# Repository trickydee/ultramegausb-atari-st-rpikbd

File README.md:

# Atari ST Keyboard (IKBD) Emulator with USB and Bluetooth support

## Overview
This project uses a Raspberry PI PICO to emulate the Atari iKBD keyboard controller and provides USB, Bluetooth and Atari 9 Pin connectivity for devices.

This is useful if you have an Atari Mega ST that is missing its keyboard or if you just want to use modern keyboards, mice and joysticks with your ST.

The emulator provides the ability to use USB or Bluetooth keyboards, mice and joysticks / gamepads with the ST. You can also use original 9 pin Dsub 'Atari' Joysticks!. 

Currently bluetooth requires a Pico 2w device - with this it is possible to Mix and Match any combination of USB, Bluetooth or 9 Pin Atari Joystick peripherals to create your perfect atari setup. If you just want USB support any Pico device will suffice.

The project is based on an an original idea created by 'fieldofcows' in 2020, this project builds on this amazing foundation to improve compatibility, stability and add support for many modern game controllers either wired USB or wireless Bluetooth connected.

A reference hardware design (KiCad schematic and PCB) for the Atari Mega ST, Mega STE, and TT computers is included in the `hardware/` directory, along with Gerber files ready for manufacture at JLCPCB or PCBWAY.

## Contributions

This project is open source and I am happy to receive pull requests and issues to further improve capabilities.

## USB Device Support

* USB HID Keyboards
* USB HID Mice
* USB HID XY Mice - Inc Microsoft Trackballs
* Logitech Unifying Adapter - Keyboard, Mice, Trackball
* Logitech Bolt Adapter - Keyboard, Mice, Trackball

## Game Controller support.
The following USB HID Gamepads/Joysticks are supported (More to come)

* PlayStation 3 DualShock 3 Controllers (including third-party PS3-compatible pads: HORI, Mad Catz, Qanba, Nacon, Logitech F310, etc.)
* PlayStation 4 DualShock 4 Controllers (including third-party PS4-compatible pads: HORI, Razer, Brook, Mad Catz, Qanba, Nacon, PowerA FightPad, etc.)
* PlayStation 5 DualSense and DualSense Edge (USB) (v21.0.3)
* PlayStation Classic (PSC) (v21.0.4)
* Xbox Xinput - Xbox One, Xbox 360 Controllers
* Nintendo Switch Pro Controller (Version 1), Joy-Con (L/R/Pair/Grip), SNES Controller (NSO)
* HORI HORIPAD for Nintendo Switch (v21.0.4)
* PowerA Fusion Wireless Arcade Stick for Nintendo Switch
* Google Stadia Controller
* Nintendo Switch / Wii U GameCube Controller USB Adapter (v11.0.0)

**v21.0.2:** Expanded USB controller support: many additional third-party PS3- and PS4-compatible VID/PIDs (same HID report format as official pads), plus Nintendo Joy-Con Charge Grip and SNES Controller (NSO).

**v21.0.3:** USB support for PlayStation 5 DualSense and DualSense Edge controllers; full joystick mapping and Llamatron dual-stick mode.

**v21.0.4:** USB support for PlayStation Classic (PSC) and HORI HORIPAD for Nintendo Switch; HORIPAD supports Llamatron dual-stick mode.

**v21.0.5:** Build fixes for GCC 15 / current ARM toolchains; `build-all.sh` continues building all board variants if Pico 2 W fails.

**v23.1.0:** Bluetooth reconnect and device-name fixes, restored gamepad routing, stable 115200-baud debug console, and updated Up/Enter/Down hardware buttons. See [release notes](RELEASE_NOTES.md) and [Bluetooth build dependencies](docs/BLUEPAD32_NATIVE_RECONNECT_TEST.md).

**v22.1.1:** Fixes mouse scroll wheel (cursor up/down) and multiple Bluetooth mice when a keyboard is paired; single `handle_keyboard()` per tick.

**v22.1.0:** OLED Devices / Map Devices UI; USB/BT device names on Map Devices; **BLE gamepad pairing fix** for Google Stadia and Xbox Wireless when BLE keyboard/mouse already connected (HID-over-GATT, flash-safe Core 1 timing).

## Bluetooth Support (Pico 2 W only)

The emulator supports Bluetooth keyboards, mice, and gamepads on the Raspberry Pi Pico 2 W (RP2350). This allows you to use wireless devices without USB cables, providing a completely wireless setup for your Atari ST.

### Supported Bluetooth Devices

* **Bluetooth Keyboards**: Standard HID keyboards with full shortcut support (Ctrl+F4, Ctrl+F11, etc.)
* **Bluetooth Mice**: Standard HID mice with scroll wheel support (scroll wheel mapped to cursor up/down keys)
* **Bluetooth Gamepads**: DualSense, DualShock 4, Switch Pro, Xbox Wireless, and more via [Bluepad32](https://github.com/ricardoquesada/bluepad32)

# Usage

## USB
For USB devices, just connect your device via the Pico's USB port using a USB OTG HUB.
The devices listed above will work a few seconds after being connected, you can confirm they are detected on the OLED screen, if you find a modern device that does not let me know via an issue ticket. 

## Bluetooth
### Pairing Bluetooth Devices

Pairing is simple - **just put your device into Bluetooth pairing mode**. The emulator will automatically detect and connect to supported devices. The emulator continuously scans for new devices, so you can pair devices at any time without needing to restart.
Most Bluetooth devices will remain paired and can be unpaired at the device ot by pressing the right - unpair button on the homescreen.

Note: During testing it has been identified that Logitech MX devices require re-pairing after each restart of the emulator.

### Bluetooth Mode Selection

On the splash screen (homescreen), you can use the **left button** to cycle between three modes:
- **USB + Bluetooth** (default): Both USB and Bluetooth devices are active simultaneously
- **USB only**: Only USB devices are used, Bluetooth is disabled
- **Bluetooth only**: Only Bluetooth devices are used, USB is disabled

### Resetting Bluetooth Pairings

If you need to clear stored Bluetooth pairing keys (for example, if a device won't reconnect or you want to re-pair from scratch), press the **right button** on the first splash screen. This will delete all stored Bluetooth pairing information, allowing you to re-pair devices from scratch.

### Bluetooth Gamepad Support

Bluetooth gamepads work just like USB gamepads:
- They appear in the joystick count alongside USB controllers
- They can be assigned to Joystick 0 or Joystick 1 via the OLED interface
- **Llamatron dual-stick mode works with Bluetooth gamepads** (requires exactly one gamepad, USB or Bluetooth)
- All keyboard shortcuts work with Bluetooth keyboards (Ctrl+F4, Ctrl+F11, etc.)

**Note**: Bluetooth support requires a Pico 2 W (RP2350). The original Pico W (RP2040) does not have enough RAM for Bluetooth support.

## Keyboard Shortcuts

The emulator supports several keyboard shortcuts for convenient control:

| Shortcut | Function | Description |
|----------|----------|-------------|
| **Ctrl+F4** | Llamatron Dual-Stick Mode | Share a single dual-stick gamepad (USB or Bluetooth) across Joystick 0 & 1 for Twinstick shooters see Llamatron Dual-Stick Mode section |
| **Ctrl+F8** | Restore Joystick Mode | Sends 0x14 to restore joystick event reporting (useful after reconnect) |
| **Ctrl+F9** | Toggle Joystick 0 | Switches Joystick 0 between D-SUB and USB |
| **Ctrl+F10** | Toggle Joystick 1 | Switches Joystick 1 between D-SUB and USB |
| **Ctrl+F11** | XRESET | Triggers HD6301 hardware reset (like power cycling the IKBD) |
| **Ctrl+F12** | Toggle Mouse Mode | Switches between USB mouse and joystick 0    * |
| **Alt+/** | INSERT Key | Sends Atari ST INSERT key (useful for sending mouse click on Logitech Mac USB keyboards) |
| **Alt+[** | Keypad /** | Sends Atari ST keypad divide key |
| **Alt+]** | Keypad *** | Sends Atari ST keypad multiply key |
| **Alt+Plus** | Set 270MHz | Overclocks RP2040 to 270MHz for maximum performance |
| **Alt+Minus** | Set 150MHz | Sets RP2040 to 150MHz for stability |

### IKBD Command Macros

For reference, these shortcut keys emit the following HD6301/IKBD command sequences:

| Shortcut | Command Sequence | Effect |
| --- | --- | --- |
| `Ctrl+F5` | `0x1A 0x00`, `0x92 0x00`, `0x08` | Disable joystick reporting, enable mouse, enter relative mode |
| `Ctrl+F6` | `0x1A 0x00`, `0x92 0x00`, `0x09 0x02 0x80 0x01 0x90` | Disable joystick, enable mouse, enter absolute mode (640×400) |
| `Ctrl+F7` | `0x1A 0x00`, `0x92 0x00`, `0x0A 0x01 0x01` | Disable joystick, enable mouse, set mouse keycode mode |
| `Ctrl+F8` | `0x14` | Restore joystick event reporting |
| `Ctrl+F11` | `XRESET` line | Full IKBD reset pulse |
| `Alt+/`, `[`, `]` | `0x52`, `0x65`, `0x66` | Insert / keypad divide / keypad multiply |

### DB-9 Mice - Joystick 0

*A real ST keyboard has a single DB-9 socket which is shared between the mouse and Joystick 0. The emulator allows you to have a mouse and joystick plugged in simultaneously but you need to select whether the mouse or joystick 0 is active. This can be toggled by pressing the **Scroll Lock** or  **Ctrl+F12** keys on the keyboard. The current mode is shown on the OLED display.

### Llamatron Dual-Stick Mode

If you love Lammatron and Robotron - Who doesnt ;-) Your going to like Lammatron mode, which enables twinstick functionality for modern controllers.

`Ctrl+F4` enables “Llamatron” mode: if exactly one gamepad (USB or Bluetooth) with two thumbsticks is connected (and both Atari joystick ports are set to USB), the left stick + face buttons continue to drive Joystick 1, the right stick transparently emulates Joystick 0 movement, and the east/right face button (Circle on PlayStation, B on Xbox, A on Switch, B on Stadia) becomes Joystick 0 fire. **How it works:**
- **Left stick** + face buttons control **Joystick 1** (movement and fire)
- **Right stick** controls **Joystick 0** movement
- **Right face button** (Circle on PlayStation, B on Xbox, A on Switch, B on Stadia) becomes **Joystick 0 fire**

**Requirements:**
- Exactly one gamepad connected (USB or Bluetooth)
- Both Atari ST joystick ports must be set to USB mode (via the OLED interface or keyboard shortcuts)
- The gamepad must have two analog thumbsticks

**Automatic deactivation:**
The mode automatically suspends itself if:
- A second gamepad is connected
- Either ST port is switched back to the DB‑9 connector
- The gamepad is disconnected

This feature works seamlessly with both USB and Bluetooth gamepads, allowing you to enjoy twin-stick shooters wirelessly on your Atari ST.

# UI Interface

The emulator displays a simple user interface on an OLED display. This is entirely optional and you can build a working version without it but
it is certainly useful to show successful connection of your USB devices as well as to allow the mouse speed to be tweaked and to view the data
flowing between the emulator and the Atari ST.

The interface is available in English, French, German, Spanish and Italian.

 &emsp;  &emsp; 

 &emsp; 

The emulator supports both USB and Atari ST compatible joysticks, supported a maximum of two joysticks at a time. Using the user interface
you can select whether the USB joystick or Atari joystick are assigned to Joysticks 0 and 1.

# Emulator Hardware

## How it works
The Atari ST keyboard contains an HD6301 microcontroller that can be programmed by the Atari TOS or by user applications to read the keyboard, mouse and joysticks. The keyboard is connected to the Atari via a serial interface (7812.5bps). Commands can be sent from the Atari to the keyboard and the keyboard sends mouse movements, keystrokes and joystick states to the Atari.

Instead of writing code to handle the serial protocol between the Atari and the keyboard, this project provides a full emulation of the HD6301 microcontroller and the hardware connected to it. This means that it appears to the Atari as a real keyboard, and can be customised and programmed by software like a real keyboard, providing maximum compatibility.

The RP2040/RP2350 USB host port or RP2350 Bluetooth is used to connect a keyboard, mouse and joysticks using a USB hub. These are translated into an emulation of the relevant device and fed into the emulated HD6301 control registers, allowing the HD6301 to determine how to communicate this with the Atari.

## Building the emulator Hardware
The emulator is configured as per the schematic below.

All of the external components *except the level shifter* are optional - you do not need to include the display and buttons if you are happy to use the keyboard shortcuts for changing settings. Also, if you only plan to use USB or Bluetooth gamepads / joysticks then you can omit the DB-9 connectors.

The level shifter is required as the Atari uses 5V logic over the serial connection whereas the Pico uses 3.3V logic.

## Hardware PCB Design - Atari Mega Adapter

A reference PCB design is available in KiCad format in the `hardware/` directory for the following Atari computers:

- **Atari Mega ST**
- **Atari Mega STE**
- **Atari TT**

The design includes:
- Complete KiCad project files (schematic and PCB layout)
- Gerber files in the `gerbers/` subdirectory
- A ready-to-upload Gerber zip file: `ultramegausb-atari-mega-adapter-2.2-gerbers.zip`

You can upload the `ultramegausb-atari-mega-adapter-2.2-gerbers.zip` file directly to PCB manufacturers such as [JLCPCB](https://jlcpcb.com/) or [PCBway](https://www.pcbway.com/) to order your own boards.

## Bill of materials

The reference adapter is very simple to construct and is also suprisingly cheap. The table below shows example pricing.
A single adapter can be made for around $20.

| Component                                             | Quantity | Required | Link / Comment                                                | Aprx Cost |
|-------------------------------------------------------|----------|----------|:--------------------------------------------------------------|----------|
| Raspberry PI Pico                                     | 1        | Y         | Pico 2040 / 2350 Module                                       | $7 |
| 1 x 20 Pin 2.54 Single Row Male Pin Header Connector   | 2        | N        | PCB Pico connector - Optional Pico may be soldered to PCB.    | inc with Pico |
| 1 x 20 Pin 2.54 Single Row Female Pin Header Connector | 2        | N        | PCB Pico connector - Optional as Pico may be soldered to PCB. | $7 for 10 |
| Bi-Directional 4 Channel logic level shifter / converter module 3.3v - 5v                           | 1        | Y        |                                                               | $7 for 10 |
| 1 x 6 Pin 2.54 Single Row Male Pin Header Connector   | 2        | Y        | PCB Voltage Regulator connector | inc with Shifter |
| 1 x RJ12 Unshielded 90 Degree push in type 6P6C connector | 1        | Y        | Atari Mega ST/TT Keyboard Connector | $9 for 30 |
| 1 x 6 Pin 2.54 Single Row Female Pin Header Connector | 2        | N        | PCB Voltage Regulator connector | $2 for 20 |
| OLED 0.96" Display 128x64 I2C SSD1306.                | 1        | N        | OLED Display - Blue / White / Yellow + Blue                                                  | $4 |
| 1 x 4 Pin 2.54 Single Row Male Pin Header Connector   | 1        | N        | OLED Connector | inc with OLED |
| Micro Push Button Switch - 6mm x 6mm x5mm             | 3        | N        | OLED Control buttons                                          | $12 for 20 |
| Micro Push Button Switch - 6mm x 6mm x5mm             | 1        | N        | Pico Reset buttons                                            | As Above |
| 1 x 4 Pin 2.54 Single Row Female Pin Header Connector | 1        | N        | PCB OLED connector | $2 for 20 |
| 9 Pin Male D-Sub Socket PCB Board Mount Connector | 2        | N        | 9 Pin Joystick Port | $10.14 for 30! |
| PCB Print at JLPCB | 1        | Y        | Example print  | $10 for 5 |

You will also need a straight through R12 to RJ12 Cable (All 6 pins connected) to connect between the Atari and the Adapter. These can be purchased pre made from Amazon (A modem cable will do if all 6 pins are terminated).

## Building/Compiling the Emulator Firmware

### Mac (ARM)  

Compiling on the mac requires xcode, gcc and arm embedded toolchain. A build can be performed with the following commands:

```bash
# Default: Pico 2 W production only (fastest for BT development)
./build-all.sh

# Incremental rebuild (keeps build/build-pico2_w/ between runs)
CLEAN_BUILD_DIRS=0 ./build-all.sh

# All boards, all in dist/
BUILD_BOARDS=all ./build-all.sh

# Debug OLED screens
DEBUG=1 ./build-all.sh

# French interface
LANGUAGE=FR ./build-all.sh

# Output (default run): dist/atari_ikbd_pico2_w_production.uf2
```

#### `build-all.sh` environment variables

| Variable | Default | Description |
|----------|---------|-------------|
| `BUILD_BOARDS` | `pico2_w` | Board(s) to build: `pico2_w`, comma-separated `pico,pico2,pico_w,pico2_w`, or `all` |
| `BUILD_VARIANT` | `production` | `production` (OLED on, minimal log), `debug` (verbose log), or `speed` (no OLED) |
| `SKIP_VARIANTS` | `1` | `1` = single variant only; `0` = after a debug build, also build production and speed |
| `CLEAN_BUILD_DIRS` | `1` | `1` = wipe build trees before/after; `0` = keep `build/build-*` for incremental rebuilds |
| `DEBUG` | `0` | `1` = debug OLED UI screens (independent of `BUILD_VARIANT`) |
| `LANGUAGE` | `EN` | `EN`, `FR`, `DE`, `SP`, or `IT` |

UF2 files are written to `dist/` with names like `atari_ikbd_pico2_w_production.uf2`. CMake trees live under `build/build-{pico|pico2|pico_w|pico2_w}/`.

PC (Linux)
```
#Install GCC
sudo apt install gcc-arm-none-eabi

#Install cmake
sudo apt install cmake

# Clone the main repo in your home folder
git clone --recursive https://github.com/trickydee/ultramegausb-atari-st-rpikbd.git

# Update submodules
cd ultramegausb-atari-st-rpikbd
git submodule update --init --recursive

# Fix missing hidparser include in CMakeLists.txt (if needed)
# Open file: ultramegausb-atari-st-rpikbd/pico-sdk/src/rp2_common/tinyusb/CMakeLists.txt
If not present, add this line after line 91:  ${PICO_TINYUSB_PATH}/src/class/hid/hidparser/HIDParser.c
You should have:

target_sources(tinyusb_host INTERFACE
            ${PICO_TINYUSB_PATH}/src/portable/raspberrypi/rp2040/hcd_rp2040.c
            ${PICO_TINYUSB_PATH}/src/portable/raspberrypi/rp2040/rp2040_usb.c
            ${PICO_TINYUSB_PATH}/src/host/usbh.c
            ${PICO_TINYUSB_PATH}/src/host/usbh_control.c
            ${PICO_TINYUSB_PATH}/src/host/hub.c
            ${PICO_TINYUSB_PATH}/src/class/cdc/cdc_host.c
            ${PICO_TINYUSB_PATH}/src/class/hid/hid_host.c
            ${PICO_TINYUSB_PATH}/src/class/hid/hidparser/HIDParser.c
            ${PICO_TINYUSB_PATH}/src/class/msc/msc_host.c
            ${PICO_TINYUSB_PATH}/src/class/vendor/vendor_host.c
            )
From your ultramegausb-atari-st-rpikbd folder:
mkdir build
cd build

# Choose one of the cmake command below according to the language and version number you want to display:
cmake -DLANGUAGE=EN .. # For English interface
or
cmake -DLANGUAGE=FR ..  # For French interface
or
cmake -DLANGUAGE=DE ..  # For German interface
or
cmake -DLANGUAGE=SP ..  # For Spanish interface
or
cmake -DLANGUAGE=IT ..  # For Italian interface

make
```

## Downloading the firmware
If you don't know how or can't build the firmware by yourself, please use the builds in the releases link.

## Using the emulator
If you build the emulator as per the schematic, the Pico is powered directly from the Atari 5V supply. The Pico boots immediately but USB enumeration can take a few seconds. Once this is complete, the emulator is fully operational.

## Emulator UI
The user interface has multiple pages that are rotated between by pressing the middle UI button. The first three pages all show the number of connected USB devices at the top but allow configuration of an option below. The pages in order are:

0. **Splash Screen** (ATARI logo): Shows firmware version and connection status. On Pico 2 W builds with Bluetooth support:
   - **Left button**: Cycles between USB+Bluetooth, USB only, and Bluetooth only modes
   - **Right button**: Deletes all stored Bluetooth pairing keys (useful for troubleshooting connection issues)

1. USB Status + Mouse speed. Left and right buttons change allow the mouse speed to be altered.

2. USB Status + Joystick 0 assignment. Left and right buttons toggle between USB joystick and DB-9 joystick.
   
    &emsp; 

3. USB Status + Joystick 1 assignment. Left and right buttons toggle between USB joystick and DB-9 joystick.
   
    &emsp; 

4. If you have a debug version deployed you will see Serial data Tx/Rx between emulator and Atari (Debug builds Only). Data received from the Atari is on the left, data sent to the Atari is on the right.

Note: The serial data page should only be used for ensuring the connection works. Displaying the page slows down the emulator and you may seem some mouse lag whilst it is active.

## USB Controller Support

The emulator supports multiple types of USB game controllers with reliable hot-swapping:

- **Xbox Controllers**: Xbox 360 (wired/wireless), Xbox One, Xbox Series X|S, Original Xbox
- **PS3 DualShock 3**: Full support via USB (wired); includes third-party PS3-compatible pads (HORI, Mad Catz, Qanba, Nacon, Logitech F310, etc.) (v10.0.0, expanded v21.0.2)
- **PS4 DualShock 4**: Full support via USB (wired); includes third-party PS4-compatible pads (HORI, Razer, Brook, Mad Catz, Qanba, Nacon, PowerA FightPad, etc.) (expanded v21.0.2)
- **PS5 DualSense / DualSense Edge**: Full support via USB (wired); D-pad, sticks, Cross/R2 fire, Llamatron dual-stick (v21.0.3)
- **PlayStation Classic (PSC)**: Full support via USB; D-pad, Cross/R2 fire; no analog sticks (v21.0.4)
- **Nintendo Switch Pro Controller**: Full support with analog stick precision and no drift; also Joy-Con (L/R/Pair/Charge Grip) and SNES Controller (NSO) (expanded v21.0.2)
- **HORI HORIPAD (Switch)**: Full support via USB; D-pad/stick, B/R2 fire; Llamatron dual-stick (v21.0.4)
- **PowerA Fusion Wireless Arcade Stick**: Full support for Nintendo Switch arcade sticks (v8.0.0)
- **Google Stadia Controller**: Full support for Stadia controllers (v8.0.0)
- **Nintendo Switch / Wii U GameCube Adapter**: Full support for official Nintendo GameCube controller USB adapter (v11.0.0)
- **Generic HID Joysticks**: Standard USB joysticks and gamepads

## Fixes
The original fieldofcows build had to fix a number of TinyUSB bugs and contained a patched branch of the TinyUSB code. This project uses the latest mainline version of Tiny USB with customizations being externalized,

This build also fixes the following bugs in the original build:
* USB devices are detected more consistenly and faster due to using the newer TinyUSB library.
* The build uses mainline Pico SDK and TinyUSB Libraries
* The Emulator now supports USB devices that enumerate multiple endpoints such as Logitech unifying and bolt adapters.
* Optimizations to Timing for the Atari RX Serial Link lowering checks from 10ms to us - fixing dropped data - 0x14 Joystick mode commands now work consistently (Great news for Ikari Warriors fans).
* Reduced Core1 6301 emulator sleep from 1ms → 250μs (4x improvement)
* Added 6301 buffer reporting.
* Enabled UART FIFO for RX and TX (32X buffer)

## Acknowledgements
The project is based on an an original idea created by 'fieldofcows' in 2020 - https://github.com/fieldofcows/atari-st-rpikb. This project builds on this great foundation to improve compatibility, stability and add support for many modern game controllers either wired USB or wireless Bluetooth connected.

The "ultramegausb" title is tongue in cheek and intended to highlight the massively enhanced capabilities made possible by the great work of TinyUSB project, Bluepad32 and associated projects listed below.

The project uses code extracted from [Steem SSE](https://sourceforge.net/projects/steemsse/). All of the work of wiring up the keyboard functions to the HD6301 CPU is credited to Steem SSE. This project contains a stripped-down version of this interface, connecting it to the Raspberry Pi's serial port.

Steem itself uses the HD6301 emulator provided by sim68xx developed by Arne Riiber. The original website for this seems to have gone but an archive can be found [here](http://www.oocities.org/thetropics/harbor/8707/simulator/sim68xx/).

The code to handle the OLED display is Copyright (c) 2021 David Schramm and taken from https://github.com/daschr/pico-ssd1306.

Bluetooth support is provided by the Bluepad32 project by Ricardo Quesada https://github.com/ricardoquesada/bluepad32.

Multi-language build support was added by Klyde https://github.com/klyde2278/atari-st-rpikb who also sells a nice kit and device to run this firmware on.

To create this ultramegausb build I also relied on the following projects for inspiration and reference implementations:

- **[tusb_xinput](https://github.com/Ryzee119/tusb_xinput)** by Ryzee119 - TinyUSB XInput host driver used for Xbox controller support
- **[BetterJoy](https://github.com/Davidobot/BetterJoy)** by Davidobot - Reference implementation for Nintendo Switch Pro Controller USB initialization and protocol handling
- **[stadia-vigem](https://github.com/walkco/stadia-vigem)** by walkco - Complete USB HID report format and button mapping for Google Stadia Controller support
- **[wii-u-gc-adapter](https://github.com/ToadKing/wii-u-gc-adapter)** by ToadKing - Linux driver for Wii U GameCube adapter, reference for USB protocol and report format
- **[osx-wiiu-gcc-adapter](https://github.com/area/osx-wiiu-gcc-adapter)** by area - macOS userspace driver for GameCube adapter using async interrupts

A large portion of the code was generated using Cursor AI and Claude LLM.

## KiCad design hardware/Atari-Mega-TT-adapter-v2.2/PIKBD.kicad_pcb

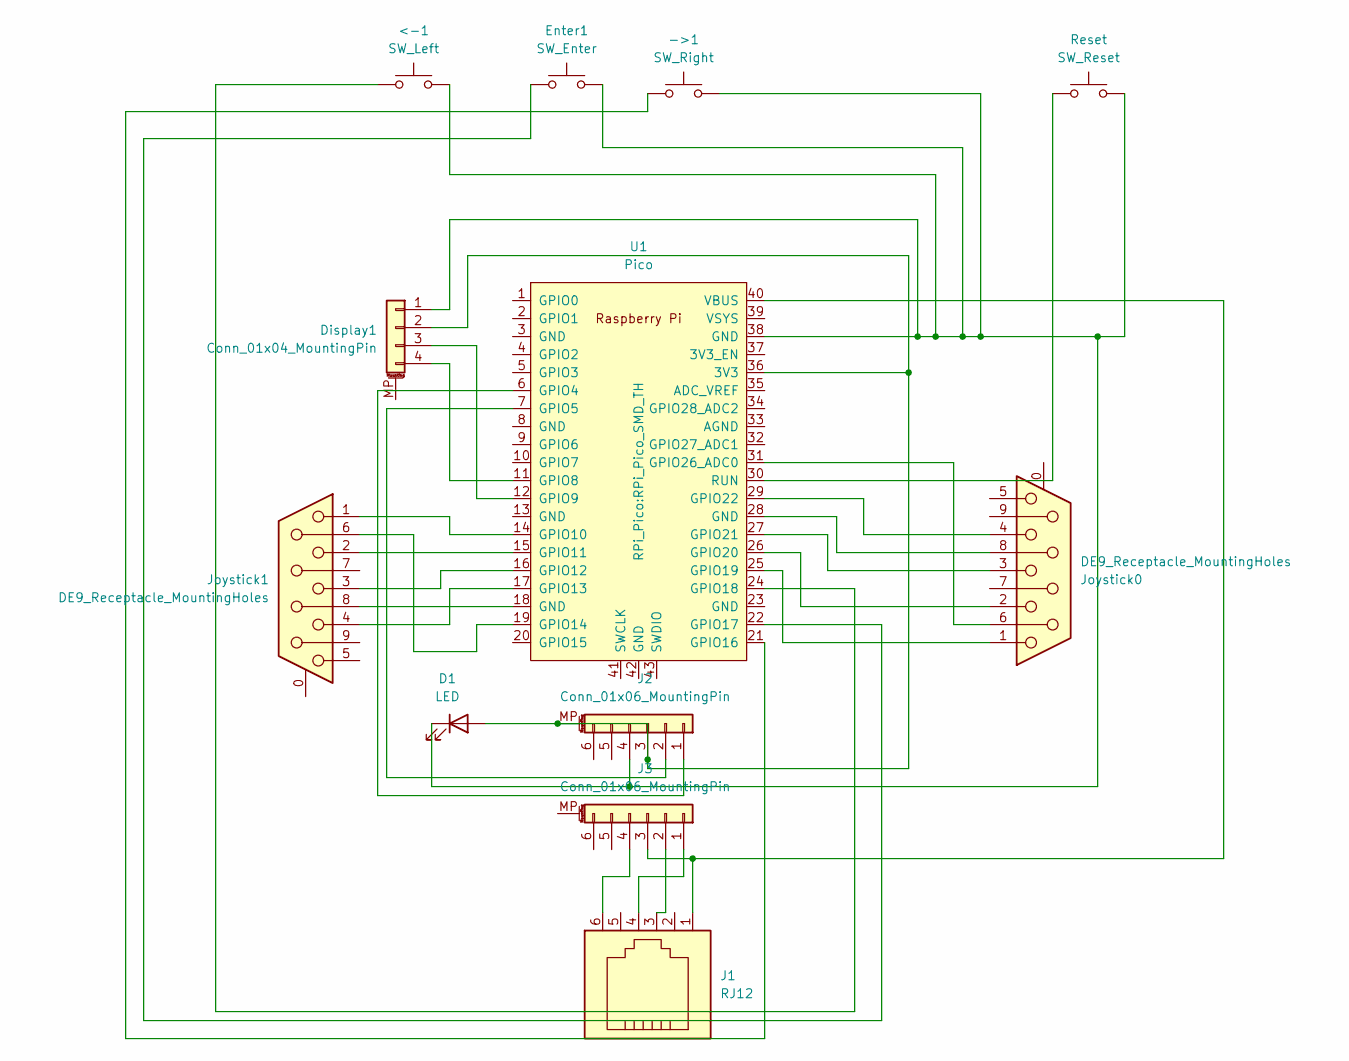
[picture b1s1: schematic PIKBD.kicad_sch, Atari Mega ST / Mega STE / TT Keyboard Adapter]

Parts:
->1: SW_Right; SW_PUSH_6mm
<-1: SW_Left; SW_PUSH_6mm
D1: LED; LED_D3.0mm
Display1: Conn_01x04_MountingPin; PinSocket_1x04_P2.54mm_Vertical
Enter1: SW_Enter; SW_PUSH_6mm
J1: RJ12; RJ12_Amphenol_54601-x06_Horizontal
J2, J3: Conn_01x06_MountingPin; PinSocket_1x06_P2.54mm_Vertical
Joystick0, Joystick1: DE9_Receptacle_MountingHoles; DSUB-9_Male_Horizontal_P2.77x2.84mm_EdgePinOffset7.70mm_Hou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
Reset: SW_Reset; SW_PUSH_6mm
U1: Pico; RPi_Pico_SMD_TH

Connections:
unnamed: D1.2 (A), Display1.2, J2.3, J2.MP (MountPin), U1.36 (3V3)
unnamed: ->1.2, <-1.2, D1.1 (K), Display1.1, Enter1.2, J2.4, Reset.2, U1.38 (GND)
unnamed: Display1.3, U1.12 (GPIO9)
unnamed: Display1.4, U1.11 (GPIO8)
unnamed: J2.1, U1.6 (GPIO4)
unnamed: J2.2, U1.7 (GPIO5)
unnamed: J1.4, J3.1
unnamed: J1.3, J3.2
unnamed: J1.1, J3.3, U1.40 (VBUS)
unnamed: J1.6, J3.4
unnamed: Joystick0.8, U1.28 (GND)
unnamed: Joystick1.8, U1.18 (GND)
unnamed: Joystick1.1, U1.14 (GPIO10)
unnamed: Joystick1.2, U1.15 (GPIO11)
unnamed: Joystick1.3, U1.16 (GPIO12)
unnamed: Joystick1.4, U1.17 (GPIO13)
unnamed: Joystick1.6, U1.19 (GPIO14)
unnamed: ->1.1, U1.21 (GPIO16)
unnamed: Enter1.1, U1.22 (GPIO17)
unnamed: <-1.1, U1.24 (GPIO18)
unnamed: Joystick0.1, U1.25 (GPIO19)
unnamed: Joystick0.2, U1.26 (GPIO20)
unnamed: Joystick0.3, U1.27 (GPIO21)
unnamed: Joystick0.4, U1.29 (GPIO22)
unnamed: Joystick0.6, U1.31 (GPIO26_ADC0)
unnamed: Reset.1, U1.30 (RUN)

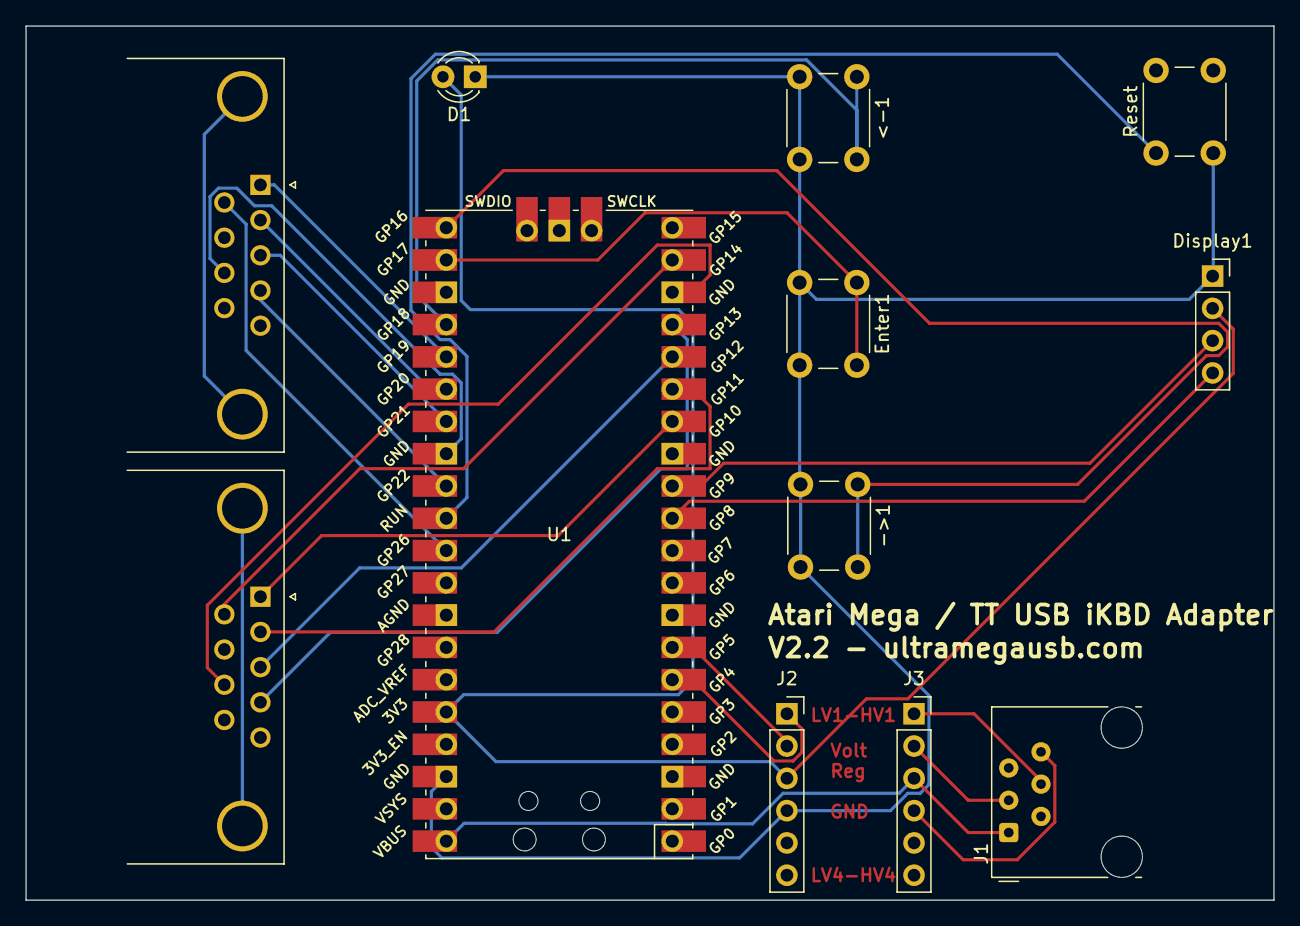
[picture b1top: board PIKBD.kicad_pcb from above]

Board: 2 copper layers, 98.2 x 68.8 mm, 12 parts (0 on the bottom side), 26 nets.

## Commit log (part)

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2025-05-20 Updates, CPU overclocked to 250mhz, USB Mouse mode configured as default (scrlck to swap
2025-05-30 Update UserInterface.h
    Added get_translation function
2025-05-30 Update README.md
    Added translated interface
2025-07-18 Update HidInput.cpp
    Added USB Joystick Dead zone
2025-10-08 Fix USB HID device detection and report handling
    - Upgrade TinyUSB from 0.10.1 to 0.12.0 for better RP2040 support
    - Fix tusb_init() return type check (bool not tusb_error_t)
    - Remove stdio_init_all() and all printf() in HID callbacks to prevent lockups
    - Add explicit tuh_hid_receive_report() calls to start report flow
    - Queue next report after each received report for continuous operation
    - Re-enable HID parser for mice and joysticks (needed for proper handling)
2025-10-08 FINAL: Upgrade to TinyUSB 0.19.0 (June 2024) - Latest Version!
    Renamed wrapper function to avoid API collision:
    - tuh_hid_get_report() → hid_app_request_report()
    - Updated all calls in HidInput.cpp
    - TinyUSB 0.19.0 repurposed tuh_hid_get_report() for control endpoint operations
    COMPLETE MODERNIZATION ACHIEVED:
    ======================================
2025-10-08 Add automated patch system for build compatibility
    - Created patches/pioasm-cmake-fix.patch to fix CMake 4.x compatibility
    - Added apply-patches.sh script to automatically apply patches
    - Updated CMakeLists.txt to run patches before building
    - Reset pico-sdk to official 1.5.1 release (no custom commits)
    - This ensures clean builds work with newer CMake versions
2025-10-11 Add dynamic clock speed control feature
    - Added Alt+Plus (=) keyboard shortcut to set clock to 270MHz
    - Added Alt+Minus (-) keyboard shortcut to set clock to 150MHz
    - Allows testing clock speed impact on joystick timing without reflashing
    - Set default clock speed to 150MHz for better timing stability
    - Prevents Alt+Plus/Minus from being sent to Atari when used for control
2025-10-14 Clean up documentation and build files
    - Add trailing newlines to markdown documentation files
    - Update pico-sdk submodule state
    - Maintain consistency across all project files
2025-10-15 Optimize HD6301 emulator Core 1 performance - v4.0.0
    Major performance improvements for IKBD command processing:
    1. Reduced CYCLES_PER_LOOP from 1000 to 250:
    - Core 1 wakes 4x more frequently (every 250μs instead of 1ms)
    - Serial interrupts processed within 250μs (was 1ms)
    - Multi-byte IKBD commands delivered 4x faster
    - ROM firmware receives command parameters promptly
2025-10-15 Xbox Controller: Add endpoint discovery and comprehensive OLED diagnostics
    Enhanced Xbox detection with automatic endpoint discovery and detailed
    OLED feedback for debugging without console access.
    Endpoint Discovery:
    - Reads configuration descriptor to find actual endpoint addresses
    - Parses descriptor to locate vendor-specific interfaces
    - Extracts IN and OUT endpoint addresses
2025-10-16 Optimize PS4 controller performance - eliminate input lag
    - Increased deadzone from 32 to 50 to eliminate stick drift
    - Removed blocking OLED updates (was updating every 50 reports)
    - Removed 3-second sleep on first report detection
    - Disabled serial debug output (printf) for performance
    - Changed debug from every 50 reports to disabled (#if 0)
    - Applied same optimizations to Xbox controller code
2025-10-16 Fix Caps Lock toggle behavior and USB LED control
    Fixed two issues with Caps Lock:
    1. Required two presses to toggle - now works on single press
    2. USB keyboard LED didn't light - now controls LED properly
    Changes:
    - Send momentary pulse to Atari ST instead of persistent state
    - capslock_send_pulse flag controls when key press is sent
2025-10-16 Fix Logitech Unifying wireless mouse detection
    Root cause: Mouse interface was detected and parsed correctly, but the
    mounted callback was only called for the first interface per device.
    On Logitech Unifying receivers:
    - Instance 0 = Keyboard (first interface, callback called)
    - Instance 1 = Mouse (second interface, callback NOT called)
    Without the mounted callback, the mouse never got added to the device
2025-10-17 Integrate official tusb_xinput driver (Ryzee119)
    Replaced custom Xbox controller detection with official tusb_xinput library:
    https://github.com/Ryzee119/tusb_xinput
    Changes:
    - Downloaded xinput_host.c and xinput_host.h from upstream
    - Added CFG_TUH_XINPUT=2 to tusb_config.h
    - Increased CFG_TUH_ENUMERATION_BUFSIZE to 512 (Xbox 360 Wireless needs >321)
2025-10-22 Update README.md for v7.5.0 and add credits
    - Updated version to 7.5.0
    - Added Nintendo Switch Pro Controller to supported controllers list
    - Added Credits section with thanks to:
    * tusb_xinput by Ryzee119 (Xbox controller support)
    * BetterJoy by Davidobot (Switch Pro Controller reference)
    - Updated controller support section with v7.5.0 features
2025-10-25 Remove QUICK_START.txt
    - Removed outdated quick start file
    - README.md now contains all necessary setup information
2025-10-25 Add automatic submodule initialization to build-all.sh
    - Check if pico-sdk is initialized before building
    - Automatically run 'git submodule update --init --recursive' if needed
    - Makes the build script self-contained for fresh checkouts
2025-10-27 Improve Switch controller splash screen and reduce init delay
    - Changed splash screen from 'SWITCH' to 'SWITCH!' (matching Xbox/PS4 style)
    - Added 2-second display time for consistency with other controllers
    - Reduced Pro Controller initialization delay from 3s to 1s
    - Faster controller initialization without compromising reliability
    - Updated UI countdown timer to reflect 1-second delay
2025-10-30 Add documentation for PowerA and v8.0 changes
2025-10-30 v9.1.0-dev: Add PS3 DualShock 3 controller support (skeleton)
    - Created ps3_controller.h with controller definitions
    - Created ps3_controller.c with basic parsing structure
    - Integrated PS3 detection into hid_app_host.c
    - Added PS3 joystick handler to HidInput.cpp
    - Updated CMakeLists.txt to include ps3_controller.c
    - Updated build-all.sh for debug mode and version
2025-11-02 Update README: Add GameCube adapter support in v11.0.0
    - Add Nintendo Switch/Wii U GameCube Controller USB Adapter to supported controllers
    - Credit ToadKing's Linux driver (wii-u-gc-adapter)
    - Credit area's macOS driver (osx-wiiu-gcc-adapter)
    - Note v11.0.0 release for GameCube adapter support
2025-11-05 chore: Bump version to 12.0.0
    Version 12.0.0 includes:
    - Ultra-low latency serial optimizations (100μs Core 1 cycles)
    - 32-byte software RX queue for zero packet loss
    - UART hardware error detection
    - Optimized 6301 emulator instruction execution
    - GameCube controller debug cleanup
2025-11-07 Tidy up markup documents
2025-11-17 remove dist content
2025-11-19 v14.0.4: Disable all GameCube debug messages for performance
    - Commented out all GC: Report, GC: Received, GC: Report callback, and GC: OUTPUT messages
    - These messages were causing serial console spam and impacting performance
    - All GameCube debug messages now completely disabled in all builds
    - Reduced frequency of GC: IN callback and GC: Processing report messages to every 100 reports
    - Bump version to 14.0.4
2025-12-14 Optimize Core 1 timing: match original 100μs delay, increase clock to 250MHz
    - Changed Core 1 delay from 300μs to 100μs to match original USB-only timing
    - Updated clock speed from 150MHz to 250MHz for Bluetooth builds
    - Updated DELAY_LOOPS calculation for 250MHz (25000 cycles = 100μs)
    - Re-enabled USB alongside Bluetooth (experimental)
    - Version bumped to 19.1.19
2025-12-16 v20.1.0: Remove debug messages and update documentation
    - Remove debug printf statements from bluepad32_atari.cpp (BUTTON_A/B detected messages)
    - Remove debug printf from HidInput.cpp (BT Joy1 messages)
    - Update BLUEPAD32_INTEGRATION.md to mark XIP and joystick indicator issues as resolved
    - Bump version to 20.1.0-blu-irq
2025-12-18 Add Pico W build support, Bluetooth guards, and heartbeat tuning
2025-12-19 v20.12.0: Add RST button to delete Bluetooth pairing keys
    - Add bluepad32_delete_pairing_keys() function for manual key deletion
    - Add RST button handler on splash screen (right button)
    - Display 'RST' label on splash screen when Bluetooth is enabled
    - Disable automatic deletion of Bluetooth keys on startup
    - Keys now persist across reboots unless manually deleted via RST button
    - Bump version to 20.12.0
2025-12-21 Expand Llamatron mode documentation with Bluetooth support details
    - Updated keyboard shortcut table to mention Bluetooth gamepad support
    - Expanded Llamatron Dual-Stick Mode section with detailed how-it-works, requirements, and automatic deactivation information
    - Clarified that Llamatron mode works with both USB and Bluetooth gamepads
    - Reorganized introduction section for better flow
2026-01-02 Add PCB design images and update README
    - Add PCB screenshot and 3D render images to docs/
    - Update README with new Usage section
    - Add images to Hardware PCB Design section
    - Improve organization with new section headings
2026-01-02 Remove old version-specific release notes files
    - Remove RELEASE_NOTES_v7.3.txt, v8.0.md, v9.0.md, v10.0.md
    - All content consolidated into unified RELEASE_NOTES.md in root
2026-01-02 Add DEVELOPER_GUIDE.md for developers and AI assistants
    - Comprehensive onboarding guide covering architecture, code organization, patterns
    - Step-by-step guide for adding new controllers with code examples
    - Key design decisions and rationale documented
    - Common patterns and conventions explained
    - Build system, dependencies, debugging, and testing guidance
    - Bridges gap between high-level summaries and detailed technical notes
2026-02-23 PS5 DualSense support and v21.0.3 (Phase 2)
    - Add PS5 DualSense and DualSense Edge USB support (VID 0x054C, PIDs 0x0CE6/0x0DF2)
    - New ps5_controller.h/c: report parsing (ID 0x01/0x31), ps5_to_atari, ps5_llamatron_axes
    - Wire into hid_app_host (mount/report/unmount) and HidInput (joystick + Llamatron)
    - Bump version to 21.0.3; update README and RELEASE_NOTES for DS5
2026-06-17 fix: GCC 15 build errors and build-all.sh early exit on Pico 2 W failure
    GCC 15 rejects implicit int and incompatible function pointer types in the
    6301 emulator; add void return types and fix instr_exec. Declare get_my_platform
    in bluepad32_init.c. Use if ! cmake patterns so set -e no longer aborts the
    multi-board build when Pico 2 W fails.
2026-06-18 perf: non-blocking USB mount splashes (P1)
    Replace sleep_ms() OLED delays in mount callbacks with a timed
    mount_splash helper so Core 0 keeps draining Atari serial during
    controller plug-in. UserInterface skips redraw while splash active.
2026-06-18 chore: release v21.0.7 — P1 input, mount splash, and mouse tuning
2026-06-18 docs: note 420e8a4 cherry-pick on picking-cherrys branch
2026-06-18 docs: 204d8b9 mouse delta accumulation verified on hardware
2026-06-19 Move CYCLES_PER_LOOP default to config.h (500).
    Drop CMake and build-all wiring; single source of truth in include/config.h.
2026-06-19 docs: flash sprint steps 1–2 verified on hardware (v21.1.1)
    Checkpoint before step 3 Core 1 resume rework.

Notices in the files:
hardware/Atari-Mega-TT-adapter-v2.2/PIKBD.kicad_sch:
(c) 2026
